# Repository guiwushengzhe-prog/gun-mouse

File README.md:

# 枪型飞鼠 · 第二代工程样机

当前配套交付为 `release/2026-10-18-最终版`。主板已迁移到嘉立创EDA专业版，后续统一在嘉立创中编辑、铺铜、检查和导出。

- 当前主板源工程：[嘉立创最终版](pcb/嘉立创最终版/枪型飞鼠最终版.eprj3)，打开时保留整个同名文件夹。
- 当前打板文件：[最终版上传打板压缩包](release/2026-10-18-最终版/枪型飞鼠_最终版_上传打板.zip)，由嘉立创原生工程导出。
- 当前打印件：[主体底座](release/2026-10-18-最终版/三维打印/主体底座.stl) 和 [摇杆支座](release/2026-10-18-最终版/三维打印/摇杆支座.stl)，各一件。
- 详细步骤：[下单与装配说明](release/2026-10-18-最终版/下单与装配说明.md)。原生工程、制板文件和打印件一并保存在最终交付目录。

下面保留早期第二代样机的设计说明；其中旧源文件和旧下单链接不再代表当前交付。

ESP32-S3 SuperMini、手焊载板和一件开放固定底座。使用手头的 SS-01GL 金属摆杆作左键，右键直接按微动本体，摇杆使用原生杆并保留中键。手指接触摆杆上的绝缘铜箔时启用体感移动，松开即停止。

第二代修正 SW1 的整组非对称孔位，保持摇杆轴心；增加直接焊在载板上的电源拨动开关，电池两根线也直接焊载板。取消塑料扳机、外置复位弹簧、调节螺丝、摇杆帽、外壳摇杆限位和粗握把。握持形状先用纸壳试，不额外打印握把。

| 目录 | 当前交付 |
|---|---|
| [pcb/](pcb/README.md) | 第二代载板：52×82 毫米、1.6 毫米厚、双面、全直插手焊；制板包、源工程、物料与接线表、1:1 套孔图、[三维预览](pcb/3d/gun-mouse-gen2.obj) |
| [shell/](shell/README.md) | 一件开放固定底座，电池与模块允许外露；手头右键帽原尺寸保留为可选件 |
| [firmware/](firmware/README.md) | 原固件与已编译镜像，鼠标按键、触摸许可和体感逻辑不变 |

## 下单与装配

1. 先将 [1:1 装配图](pcb/carrier-assembly-map-1to1.pdf) 按实际尺寸打印，用手头 SW1 从标示的安装面套孔。此次修正依据原厂孔图与第一代实物反馈，尚未进行第二代实物插装。
2. 上传 [第二代嘉立创制板包](pcb/gun-mouse-supermini-carrier-JLC-Gerber.zip)。常规 FR-4、双面、1.6 毫米、1 盎司铜；只做裸板，不做贴片装配。板框有缺口，以文件轮廓为准。
3. 只需新增打印 [开放底座](shell/stl/engineering_mount.stl)，毫米、100% 比例。手头旧小件不用重新打印；右键帽可留作后续手感试验。
4. 按 [载板说明](pcb/README.md) 焊元件与模块线，电池开关置关后通过 USB 烧录并检查，再固定到底座。SS-01GL 的公共端、常开端仍用两根软线接载板。
5. 金属摆杆上依次贴薄绝缘胶带、铜箔、表面绝缘胶带。铜箔只连接触摸焊盘，导线不牵拉摆杆；贴好后实测触摸和回弹。电池、模块固定及供电限制见 [底座装配说明](shell/README.md)。

## 版本与验收范围

当前目录只列第二代交付，第一代保存在 Git 提交 `9e3d071` 中。电路设计检查、名义几何检查与实物试装、通电验收分别记录，不能用软件检查代替摇杆实物插装、触摸灵敏度、充电和握持验收。

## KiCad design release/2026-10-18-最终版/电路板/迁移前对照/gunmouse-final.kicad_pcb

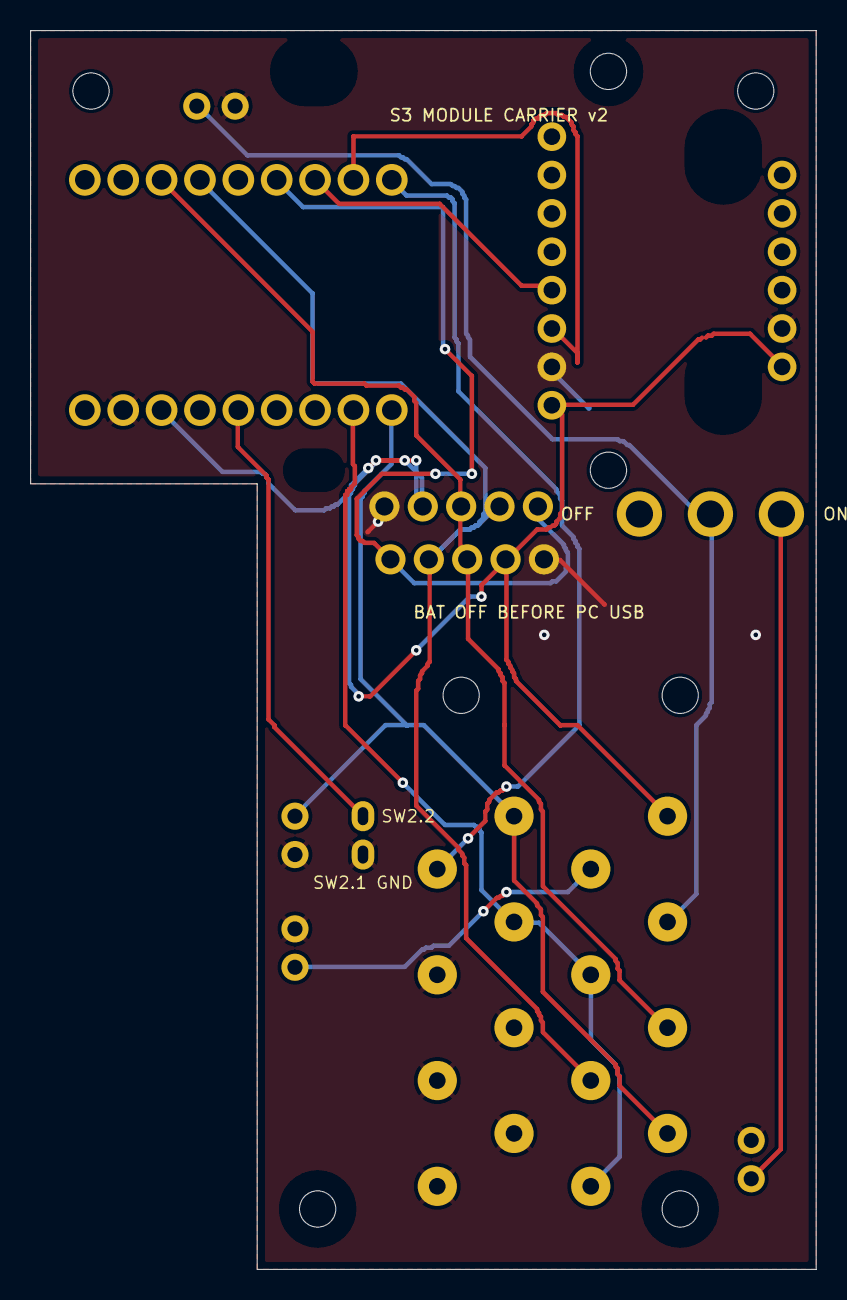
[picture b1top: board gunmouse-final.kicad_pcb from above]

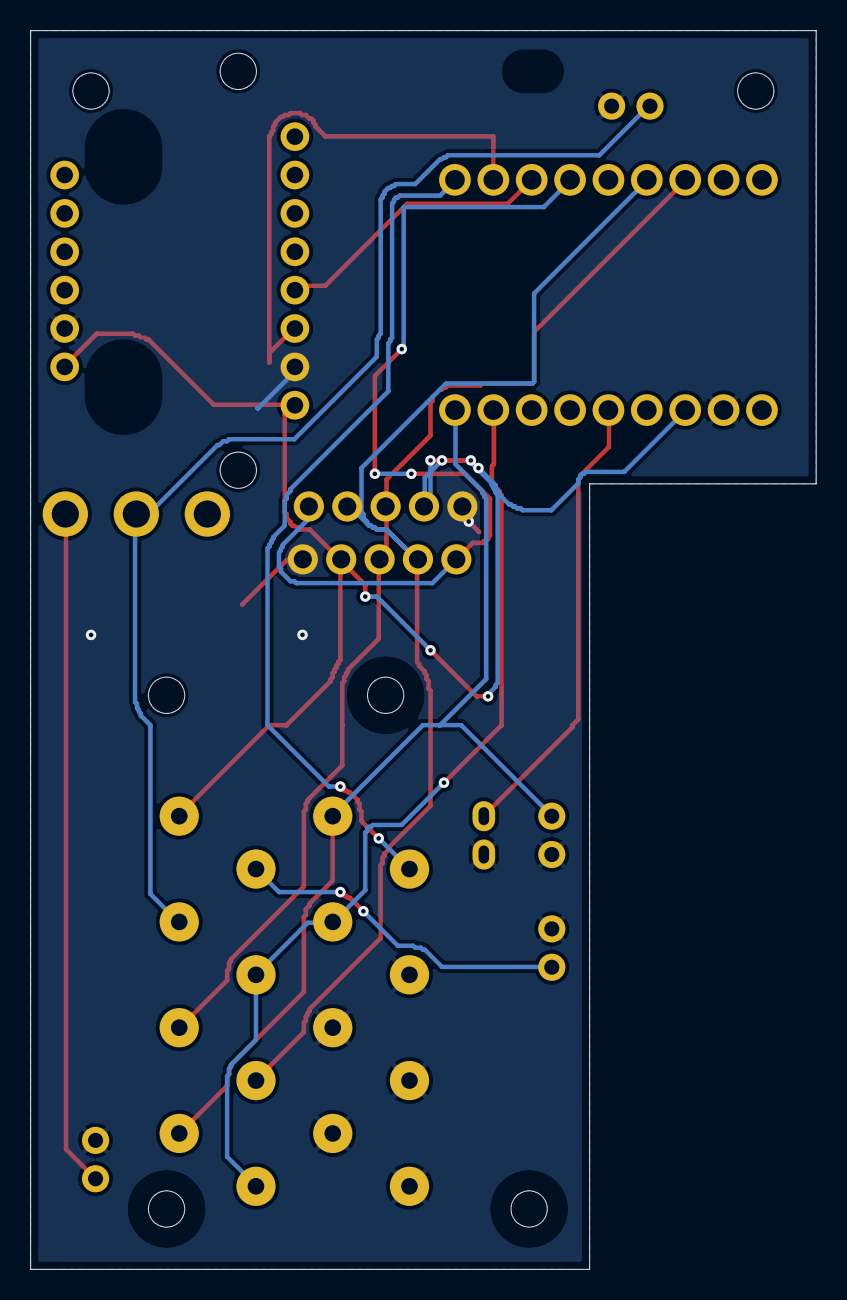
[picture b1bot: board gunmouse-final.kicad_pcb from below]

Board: 2 copper layers, 52.0 x 82.0 mm, 26 parts (16 on the bottom side), 14 nets.

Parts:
C_BAT: 100n; C_BAT
C_JOY_X: 100n; C_JOY_X
C_JOY_Y: 100n; C_JOY_Y
C_TRIG: 100n; C_TRIG
H1, H2, H3, H4: M2 clearance 2.4 mm; Mount_M2
H_BODY_5: (no value)
H_IMU_1, H_IMU_2: (no value)
H_JOY_LOCAL_2: (no value)
J_BAT: Labelled solder wires; J_BAT
J_GY: GY-601N1-LSM6DSV16X 8+6; J_GY
J_MCU: ESP32-S3 SuperMini 2x9; J_MCU
J_MODULE_BAT: Labelled solder wires; J_MODULE_BAT
J_SWITCH: SS12D10 G5; J_SWITCH
J_TOUCH: Labelled solder wires; J_TOUCH
J_TRIG: Labelled solder wires; J_TRIG
R_BAT_H: 100k; R_BAT_H
R_BAT_L: 100k; R_BAT_L
R_TOUCH: 510; R_TOUCH
R_TRIG: 3.3k; R_TRIG
SW1: HW-504 34x26mm; SW1
SW1_ALT: HW-504直排针备用位; SW1_ALT
SW2: 右键软线接点; SW2

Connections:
3V3: J_GY.1, J_GY.14, J_MCU.12, R_TRIG.1, SW1.2, SW1_ALT.4
BAT_RAW: J_BAT.1, J_SWITCH.1
BAT_SW: J_MODULE_BAT.1, J_SWITCH.2, R_BAT_H.1
BTN_R: J_MCU.14, SW2.2
GND: C_BAT.2, C_JOY_X.2, C_JOY_Y.2, C_TRIG.2, J_BAT.2, J_GY.2, J_GY.13, J_MCU.11, J_MODULE_BAT.2, J_TOUCH.2, J_TRIG.1, R_BAT_L.2, SW1.1, SW1_ALT.5, SW2.1
JOY_SW: J_MCU.6, SW1.5, SW1_ALT.1
JOY_X: C_JOY_X.1, J_MCU.3, SW1.3, SW1_ALT.3
JOY_Y: C_JOY_Y.1, J_MCU.4, SW1.4, SW1_ALT.2
SCL: J_GY.3, J_MCU.8
SDA: J_GY.4, J_MCU.7
TOUCH: J_MCU.9, R_TOUCH.2
TOUCH_ELECTRODE: J_TOUCH.1, R_TOUCH.1
TRIG: C_TRIG.1, J_MCU.18, J_TRIG.2, R_TRIG.2
VBAT_ADC: C_BAT.1, J_MCU.17, R_BAT_H.2, R_BAT_L.1

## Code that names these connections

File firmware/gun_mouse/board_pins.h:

#pragma once

// 由 generate_board_pins.py 从正式主板配置生成，禁止手工改引脚。
// 排针编号依据厂家 YD-ESP32-S3 电路图 V1.4。
// 配置SHA256: 7fe80e1e2e066cec1c183877b920eb5e2993332164d19e1b66ddfe4d19ce390b
namespace GunMouse {
namespace Pins {
constexpr int BTN_R = 15;
constexpr int IMU_INT1 = 10;
constexpr int IMU_INT2 = 11;
constexpr int JOY_SW = 6;
constexpr int JOY_X = 4;
constexpr int JOY_Y = 5;
constexpr int SCL = 9;
constexpr int SDA = 8;
constexpr int TOUCH = 14;
constexpr int TRIG = 16;
constexpr int USB_DN = 19;
constexpr int USB_DP = 20;
constexpr int VBAT_ADC = 1;
constexpr int VBUS_DET = 2;
// VBUS_DET使用模拟采样；触摸S3读数触摸时上升。
}  // namespace Pins
}  // namespace GunMouse
